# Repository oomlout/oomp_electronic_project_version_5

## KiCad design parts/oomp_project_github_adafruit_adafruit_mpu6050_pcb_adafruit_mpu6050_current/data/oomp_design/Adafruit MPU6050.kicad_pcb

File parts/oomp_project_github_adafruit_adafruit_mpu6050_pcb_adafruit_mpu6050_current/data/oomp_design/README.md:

# OOMP KiCad design copy

Open `Adafruit MPU6050.kicad_pro` (or the `.kicad_pcb` / `.kicad_sch`) in KiCad. Local OOMP libraries are under `libraries/`. Original inputs are preserved in [../original/](../original/).

Only verified unchanged installed KiCad defaults were renamed. Modified, custom, unmatched and unavailable items remain unchanged. Soldering variants are never swapped during conversion. Existing pad coordinates, nets and UUIDs are preserved.

See [conversion_report.yaml](conversion_report.yaml) for every conversion and skip. Copy this directory before editing; regeneration refuses to overwrite edited design files.

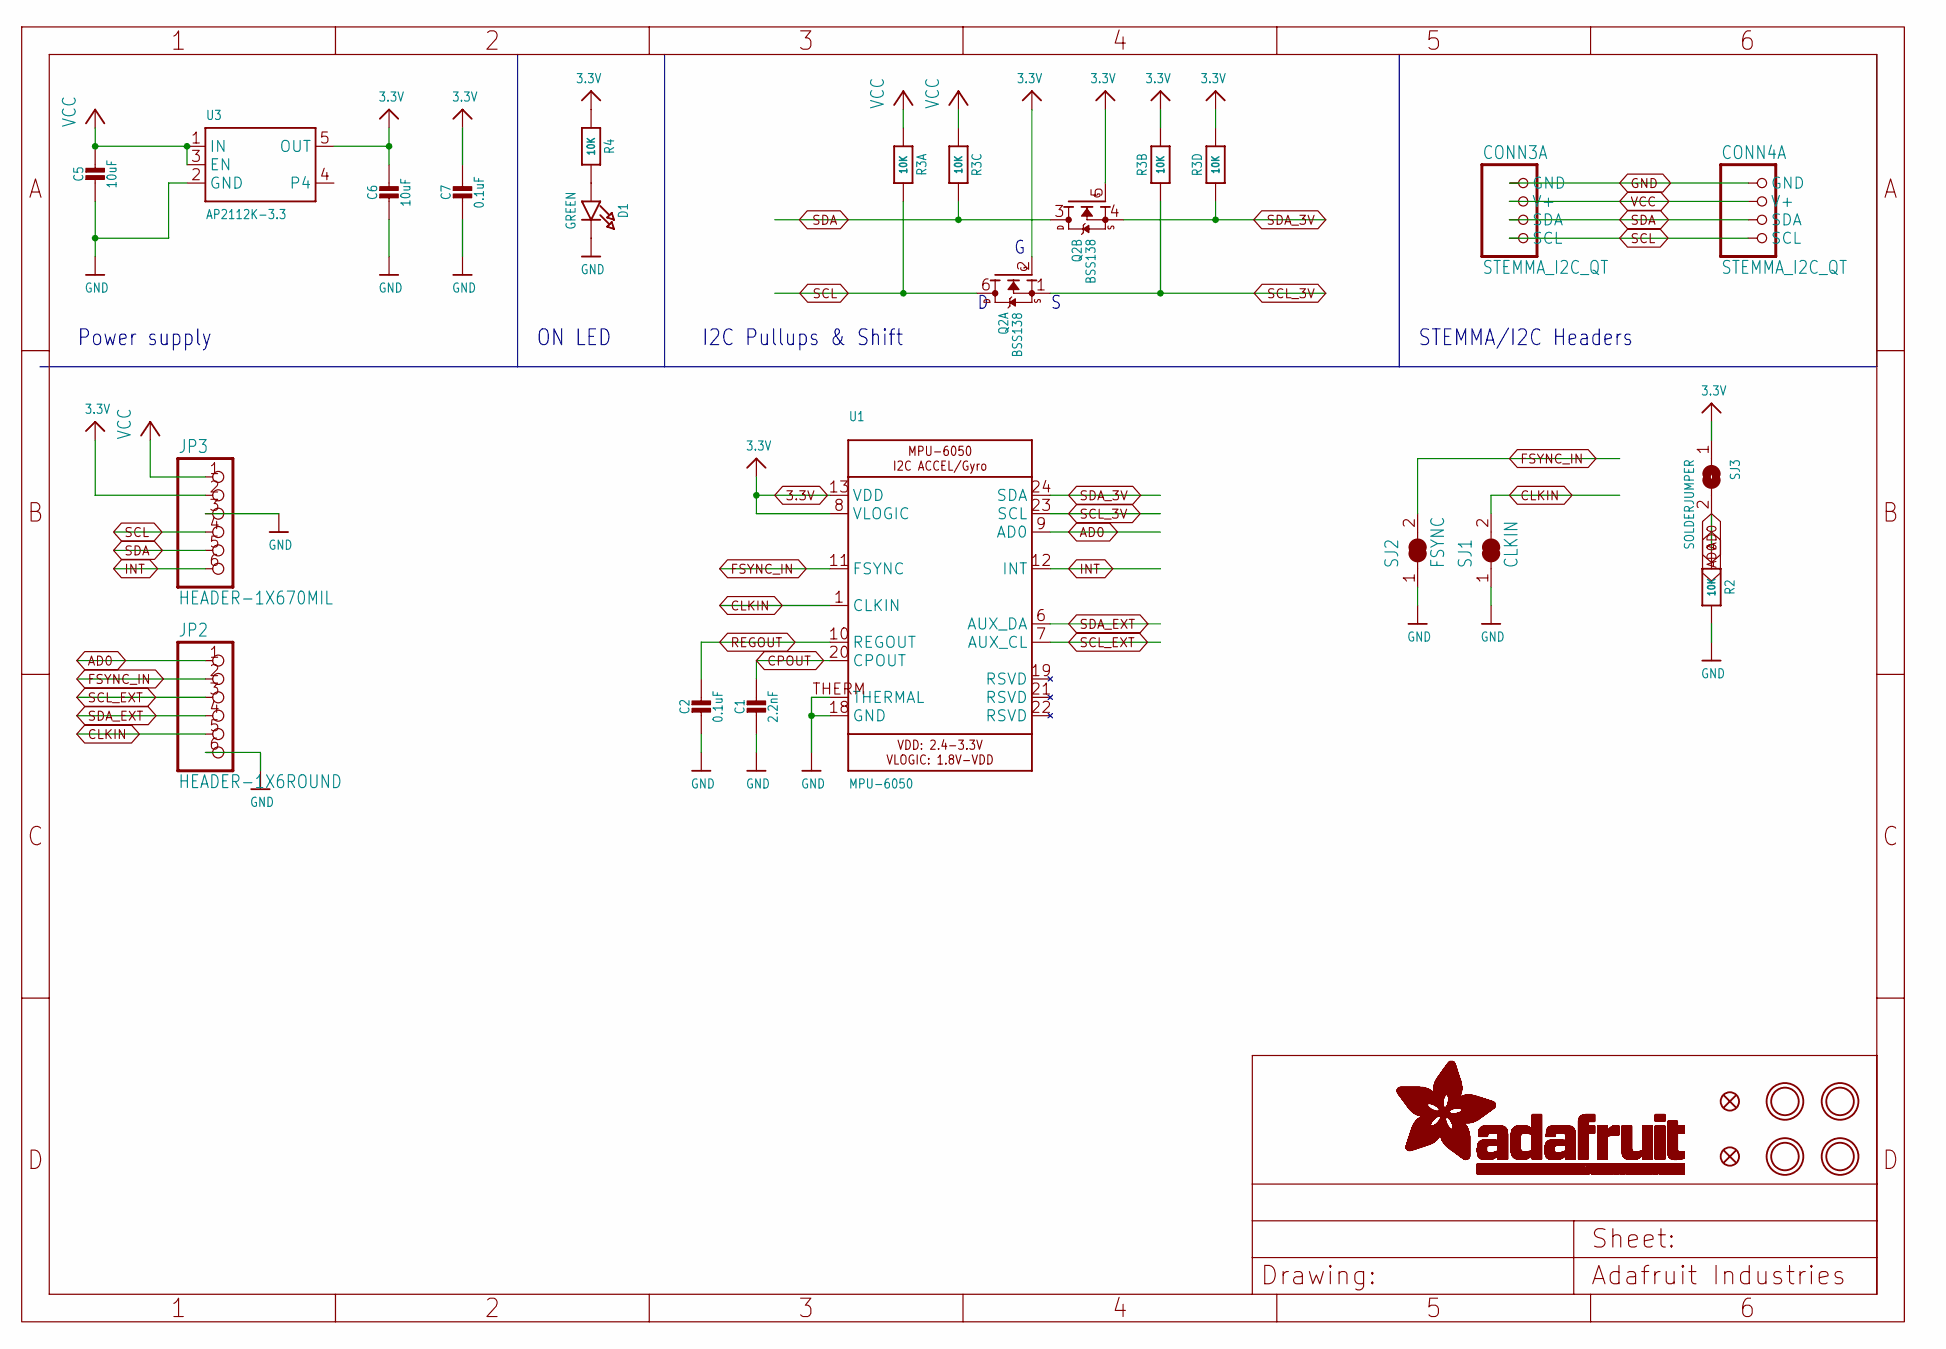
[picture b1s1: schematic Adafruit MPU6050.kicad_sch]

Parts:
C1: 2.2nF; 0603-NO
C2, C7: 0.1uF; 0603-NO
C5, C6: 10uF; 0805-NO
CONN3, CONN4: STEMMA_I2C_QT; JST_SH4
D1: GREEN; CHIPLED_0603_NOOUTLINE
FID3, FID4: FIDUCIAL_1MM
JP2: HEADER-1X6ROUND; 1X06_ROUND
JP3: HEADER-1X670MIL; 1X06_ROUND_70
Q2: BSS138; SOT363
R2, R4: 10K; 0603-NO
R3: 10K; RESPACK_4X0603
SJ1: CLKIN; SOLDERJUMPER_CLOSEDWIRE
SJ2: FSYNC; SOLDERJUMPER_CLOSEDWIRE
SJ3: SOLDERJUMPER; SOLDERJUMPER_ARROW_NOPASTE
U1: MPU-6050; QFN24_4MM_SMSC
U3: AP2112K-3.3; SOT23-5
U$39, U$40, U$42, U$43: MOUNTINGHOLE2.5; MOUNTINGHOLE_2.5_PLATED

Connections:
3.3V: C6.1, C7.1, JP3.2, Q2.2 (G), Q2.5 (G), R3.2 (1), R3.4 (1), R4.1, SJ3.1, U1.8 (VLOGIC), U1.13 (VDD), U3.5 (OUT)
AD0: JP2.1, R2.1, SJ3.2, U1.9 (AD0)
CLKIN: JP2.5, SJ1.2, U1.1 (CLKIN)
CPOUT: C1.1, U1.20 (CPOUT)
FSYNC_IN: JP2.2, SJ2.2, U1.11 (FSYNC)
GND: C1.2, C2.2, C5.2, C6.2, C7.2, CONN3.1 (GND), CONN4.1 (GND), D1.C, JP2.6, JP3.3, R2.2, SJ1.1, SJ2.1, U1.18 (GND), U1.THERM (THERMAL), U3.2 (GND)
INT: JP3.6, U1.12 (INT)
unnamed: D1.A, R4.2
REGOUT: C2.1, U1.10 (REGOUT)
SCL: CONN3.4 (SCL), CONN4.4 (SCL), JP3.4, Q2.6 (D), R3.8 (2)
SCL_3V: Q2.1 (S), R3.7 (2), U1.23 (SCL)
SCL_EXT: JP2.3, U1.7 (AUX_CL)
SDA: CONN3.3 (SDA), CONN4.3 (SDA), JP3.5, Q2.3 (D), R3.6 (2)
SDA_3V: Q2.4 (S), R3.5 (2), U1.24 (SDA)
SDA_EXT: JP2.4, U1.6 (AUX_DA)
VCC: C5.1, CONN3.2 (V+), CONN4.2 (V+), JP3.1, R3.1, R3.3 (1), U3.1 (IN), U3.3 (EN)

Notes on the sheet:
Power supply
STEMMA/I2C Headers
ON LED
I2C Pullups & Shift

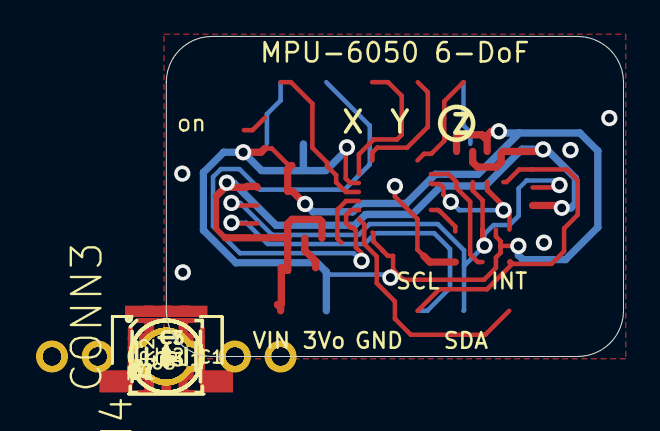
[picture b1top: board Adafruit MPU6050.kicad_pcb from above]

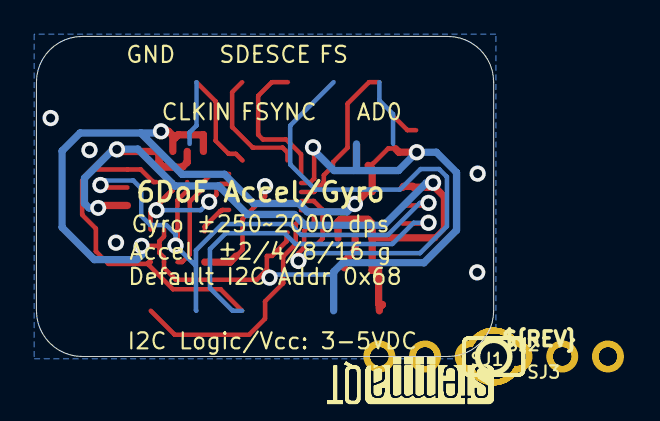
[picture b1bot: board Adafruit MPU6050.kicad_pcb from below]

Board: 2 copper layers, 25.4 x 17.8 mm, 28 parts (6 on the bottom side), 16 nets.

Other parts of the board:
U$46: PCBFEAT-REV-040
U$47, U$48: STEMMAQT

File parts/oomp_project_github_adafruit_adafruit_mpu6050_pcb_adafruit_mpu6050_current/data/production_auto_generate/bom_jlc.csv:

Comment,Designator,Footprint,LCSC Part #
,JP2,Adafruit MPU6050-import-fps:1X06_ROUND,C37208
,JP3,Adafruit MPU6050-import-fps:1X06_ROUND_70,C37208
,U$46,Adafruit MPU6050-import-fps:PCBFEAT-REV-040,
,"U$47,U$48",Adafruit MPU6050-import-fps:STEMMAQT,
0.1uF,"C2,C7",Adafruit MPU6050-import-fps:0603-NO,C14663
10K,"R2,R4",Adafruit MPU6050-import-fps:0603-NO,C98220
10K,R3,Adafruit MPU6050-import-fps:RESPACK_4X0603,C98220
10uF,"C5,C6",Adafruit MPU6050-import-fps:0805-NO,
2.2nF,C1,Adafruit MPU6050-import-fps:0603-NO,
AP2112K-3.3,U3,Adafruit MPU6050-import-fps:SOT23-5,
BSS138,Q2,Adafruit MPU6050-import-fps:SOT363,
GREEN,D1,Adafruit MPU6050-import-fps:CHIPLED_0603_NOOUTLINE,
MPU-6050,U1,Adafruit MPU6050-import-fps:QFN24_4MM_SMSC,
STEMMA_I2C_QT,"CONN3,CONN4",Adafruit MPU6050-import-fps:JST_SH4,C160404

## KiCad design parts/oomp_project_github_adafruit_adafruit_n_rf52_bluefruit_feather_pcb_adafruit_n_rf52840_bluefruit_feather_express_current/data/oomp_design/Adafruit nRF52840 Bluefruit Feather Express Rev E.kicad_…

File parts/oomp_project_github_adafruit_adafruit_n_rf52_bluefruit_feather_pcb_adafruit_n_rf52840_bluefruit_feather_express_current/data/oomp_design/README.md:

# OOMP KiCad design copy

Open `Adafruit nRF52840 Bluefruit Feather Express Rev E.kicad_pro` (or the `.kicad_pcb` / `.kicad_sch`) in KiCad. Local OOMP libraries are under `libraries/`. Original inputs are preserved in [../original/](../original/).

Only verified unchanged installed KiCad defaults were renamed. Modified, custom, unmatched and unavailable items remain unchanged. Soldering variants are never swapped during conversion. Existing pad coordinates, nets and UUIDs are preserved.

See [conversion_report.yaml](conversion_report.yaml) for every conversion and skip. Copy this directory before editing; regeneration refuses to overwrite edited design files.

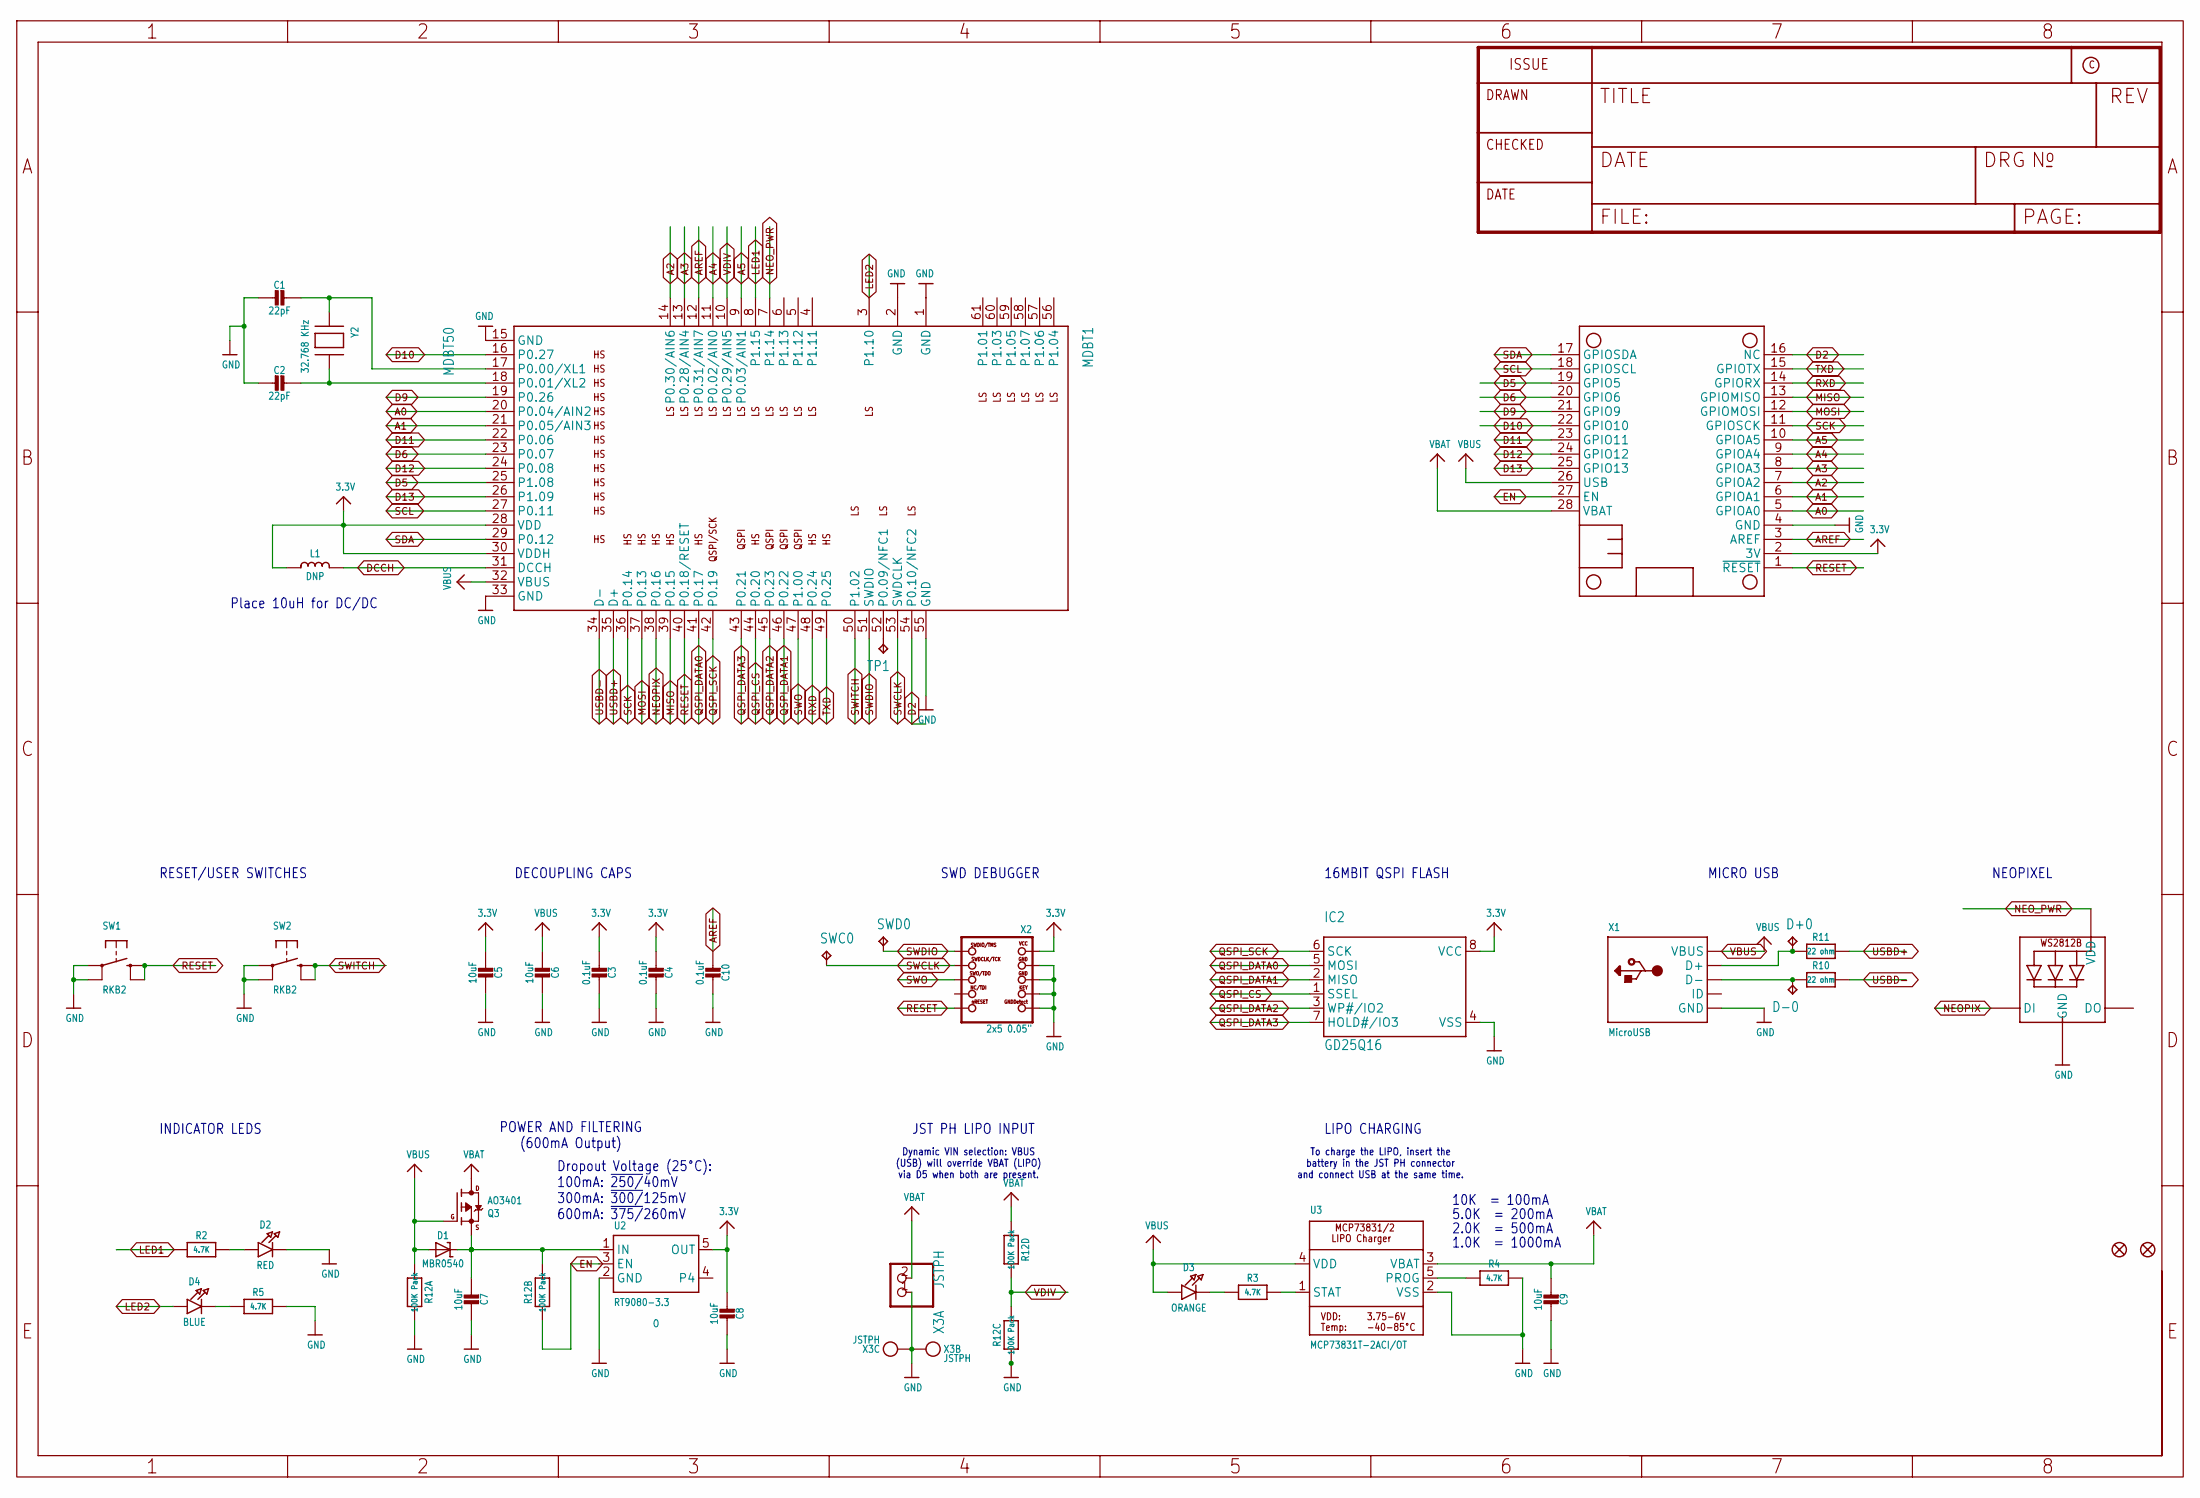
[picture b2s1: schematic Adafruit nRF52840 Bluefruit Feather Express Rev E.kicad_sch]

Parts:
C1, C2: 22pF; 0603-NO
C3, C4, C10: 0.1uF; 0603-NO
C5, C6, C7, C8, C9: 10uF; 0805-NO
D1: MBR0540; SOD-123
D2: RED; CHIPLED_0603_NOOUTLINE
D3: ORANGE; CHIPLED_0603_NOOUTLINE
D4: BLUE; CHIPLED_0603_NOOUTLINE
D+0: TPTP10R; TP10R
D-0: TPTP10R; TP10R
FID1, FID2: FIDUCIAL_1MM
IC2: GD25Q16; USON8
L1: DNP; _0805MP
LED1: WS2812B_3535FULL; LED3535_FULLPADS
MDBT1: MDBT50
MS1: FEATHERWING_NODIM
Q3: AO3401; SOT23-R
R2, R3, R4, R5: 4.7K; 0603-NO
R10, R11: 22 ohm; _0603MP
R12: 100K Pack; RESPACK_4X0603
SW1, SW2: RKB2; BTN_RKB2_4.6X2.8
SWC0: TPTP12R; TP12R
SWD0: TPTP12R; TP12R
TP1: TPTP10R; TP10R
U2: RT9080-3.3; SOT23-5; JLC_ROTATION 0
U3: MCP73831T-2ACI/OT; SOT23-5; JLC_ROTATION 0
X1: MicroUSB; 4UCONN_20329_V2
X2: 2x5 0.05"; 2X05_1.27MM_BOX_POSTS
X3: JSTPH; JSTPH2_BATT; LCSC C47647
Y2: 32.768 KHz; XTAL3215

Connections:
3.3V: C3.2, C4.2, C5.2, C8.2, IC2.8 (VCC), L1.1, MDBT1.28 (VDD), MDBT1.30 (VDDH), MS1.2 (3V), U2.5 (OUT), X2.1 (VCC)
A0: MDBT1.20 (P0.04/AIN2), MS1.5 (GPIOA0)
A1: MDBT1.21 (P0.05/AIN3), MS1.6 (GPIOA1)
A2: MDBT1.14 (P0.30/AIN6), MS1.7 (GPIOA2)
A3: MDBT1.13 (P0.28/AIN4), MS1.8 (GPIOA3)
A4: MDBT1.11 (P0.02/AIN0), MS1.9 (GPIOA4)
A5: MDBT1.9 (P0.03/AIN1), MS1.10 (GPIOA5)
AREF: C10.2, MDBT1.12 (P0.31/AIN7), MS1.3 (AREF)
D2: MDBT1.54 (P0.10/NFC2), MS1.16 (NC)
D5: MDBT1.25 (P1.08), MS1.19 (GPIO5)
D6: MDBT1.23 (P0.07), MS1.20 (GPIO6)
D9: MDBT1.19 (P0.26), MS1.21 (GPIO9)
D10: MDBT1.16 (P0.27), MS1.22 (GPIO10)
D11: MDBT1.22 (P0.06), MS1.23 (GPIO11)
D12: MDBT1.24 (P0.08), MS1.24 (GPIO12)
D13: MDBT1.26 (P1.09), MS1.25 (GPIO13)
D+: D+0.TP, R11.1, X1.D+
D-: D-0.TP, R10.1, X1.D-
DCCH: L1.2, MDBT1.31 (DCCH)
EN: MS1.27 (EN), R12.2 (1), U2.3 (EN)
GND: C1.2, C2.2, C3.1, C4.1, C5.1, C6.1, C7.1, C8.1, C9.1, C10.1, D2.C, IC2.4 (VSS), LED1.4 (GND), MDBT1.1 (GND), MDBT1.2 (GND), MDBT1.15 (GND), MDBT1.33 (GND), MDBT1.55 (GND), MS1.4 (GND), R4.2, R5.2, R12.3 (1), R12.8 (2), SW1.A, SW1.A' (P1), SW2.A, SW2.A' (P1), U2.2 (GND), U3.2 (VSS), X1.BASE@1 (GND), X1.BASE@2 (GND), X1.GND, X1.SPRT@1 (GND), X1.SPRT@2 (GND), X1.SPRT@3 (GND), X1.SPRT@4 (GND), X2.3 (GND), X2.5 (GND), X2.7 (KEY), X2.9 (GNDDETECT), X3.1, X3.NC1, X3.NC2
LED1: MDBT1.8 (P1.15), R2.1
LED2: D4.A, MDBT1.3 (P1.10)
MISO: MDBT1.39 (P0.15), MS1.13 (GPIOMISO)
MOSI: MDBT1.37 (P0.13), MS1.12 (GPIOMOSI)
unnamed: D3.C, R3.1
unnamed: D2.A, R2.2
unnamed: C1.1, MDBT1.17 (P0.00/XL1), Y2.P$1
unnamed: C2.1, MDBT1.18 (P0.01/XL2), Y2.P$2
unnamed: R3.2, U3.1 (STAT)
unnamed: R4.1, U3.5 (PROG)
unnamed: D4.C, R5.1
NEOPIX: LED1.1 (DI), MDBT1.38 (P0.16)
NEO_PWR: LED1.2 (VDD), MDBT1.7 (P1.14)
NFC2: MDBT1.52 (P0.09/NFC1), TP1.TP
QSPI_CS: IC2.1 (SSEL), MDBT1.44 (P0.20)
QSPI_DATA0: IC2.5 (MOSI), MDBT1.41 (P0.17)
QSPI_DATA1: IC2.2 (MISO), MDBT1.46 (P0.22)
QSPI_DATA2: IC2.3 (WP#/IO2), MDBT1.45 (P0.23)
QSPI_DATA3: IC2.7 (HOLD#/IO3), MDBT1.43 (P0.21)
QSPI_SCK: IC2.6 (SCK), MDBT1.42 (P0.19)
RESET: MDBT1.40 (P0.18/RESET), MS1.1 (~RESET), SW1.B (S), SW1.B' (S1), X2.10 (NRESET)
RXD: MDBT1.48 (P0.24), MS1.14 (GPIORX)
SCK: MDBT1.36 (P0.14), MS1.11 (GPIOSCK)
SCL: MDBT1.27 (P0.11), MS1.18 (GPIOSCL)
SDA: MDBT1.29 (P0.12), MS1.17 (GPIOSDA)
SWCLK: MDBT1.53 (SWDCLK), SWC0.TP, X2.4 (SWDCLK)
SWDIO: MDBT1.51 (SWDIO), SWD0.TP, X2.2 (SWDIO)
SWITCH: MDBT1.50 (P1.02), SW2.B (S), SW2.B' (S1)
SWO: MDBT1.47 (P1.00), X2.6 (SWO)
TXD: MDBT1.49 (P0.25), MS1.15 (GPIOTX)
USBD+: MDBT1.35 (D+), R11.2
USBD-: MDBT1.34 (D-), R10.2
VBAT: C9.2, MS1.28 (VBAT), Q3.3 (D), R12.4 (1), U3.3 (VBAT), X3.2
VBUS: C6.2, D1.A, D3.A, MDBT1.32 (VBUS), MS1.26 (USB), Q3.1 (G), R12.1, U3.4 (VDD), X1.VBUS
VDIV: MDBT1.10 (P0.29/AIN5), R12.5 (2), R12.6 (2)
VHI: C7.2, D1.C, Q3.2 (S), R12.7 (2), U2.1 (IN)

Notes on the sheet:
NEOPIXEL
Dynamic VIN selection: VBUS (USB) will override VBAT (LIPO) via D5 when both are present.
SWD DEBUGGER
Dropout Voltage (25°C): 100mA: ~{250/}40mV 300mA: ~{300/}125mV 600mA: ~{375/}260mV
10K = 100mA
RESET/USER SWITCHES
INDICATOR LEDS
MICRO USB
DECOUPLING CAPS
To charge the LIPO, insert the battery in the JST PH connector and connect USB at the same time.
JST PH LIPO INPUT
LIPO CHARGING
POWER AND FILTERING (600mA Output)
16MBIT QSPI FLASH
Place 10uH for DC/DC
2.0K = 500mA
1.0K = 1000mA
5.0K = 200mA

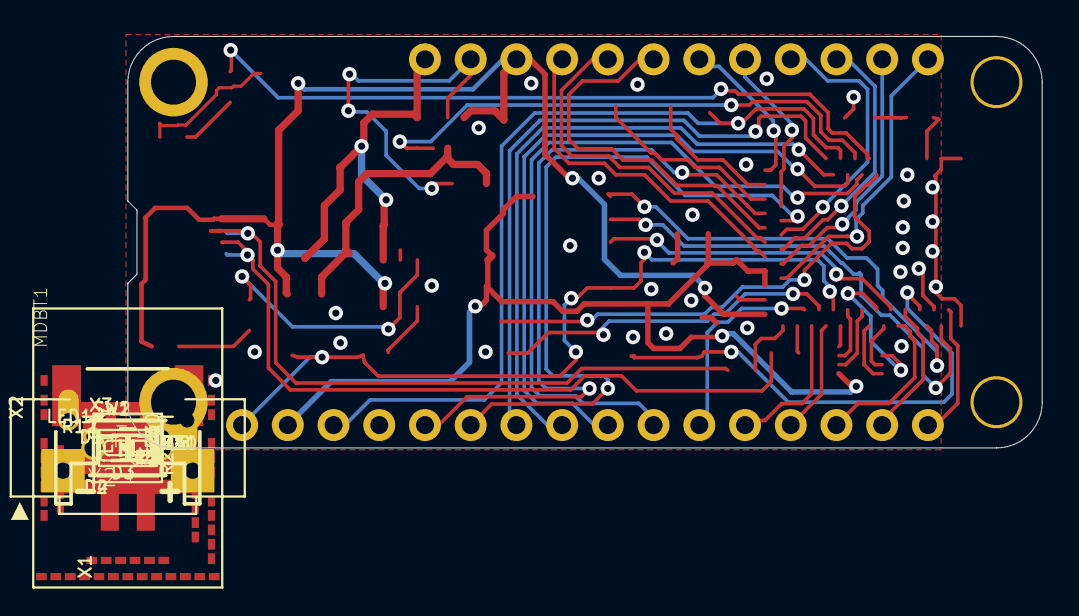
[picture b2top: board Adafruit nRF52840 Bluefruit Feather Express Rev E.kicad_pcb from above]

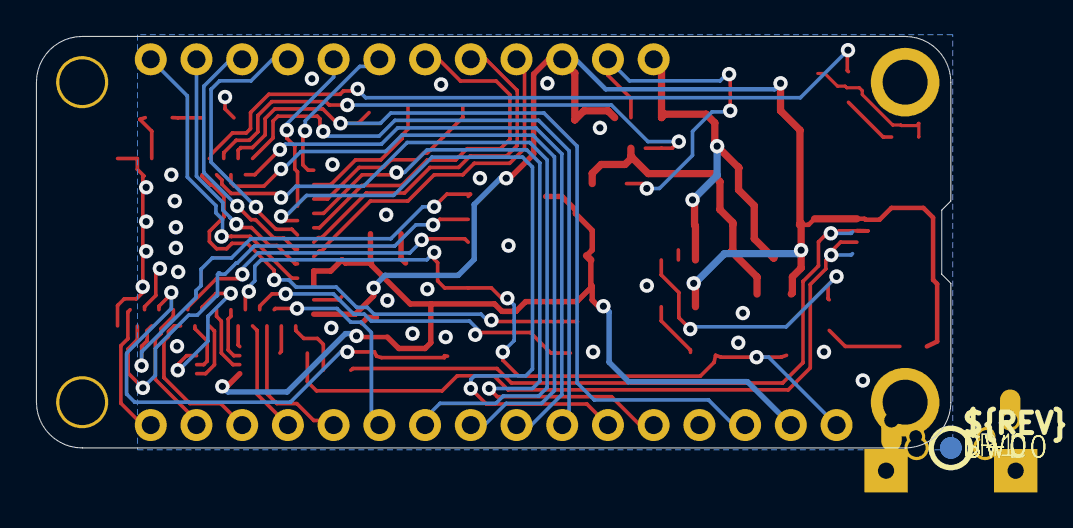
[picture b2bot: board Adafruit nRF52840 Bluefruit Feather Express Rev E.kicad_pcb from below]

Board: 2 copper layers, 50.8 x 22.9 mm, 45 parts (7 on the bottom side), 57 nets.

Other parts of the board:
U$10: PCBFEAT-REV-056
U$12: NRF52840_BOT
U$14: NRF52840_TOP

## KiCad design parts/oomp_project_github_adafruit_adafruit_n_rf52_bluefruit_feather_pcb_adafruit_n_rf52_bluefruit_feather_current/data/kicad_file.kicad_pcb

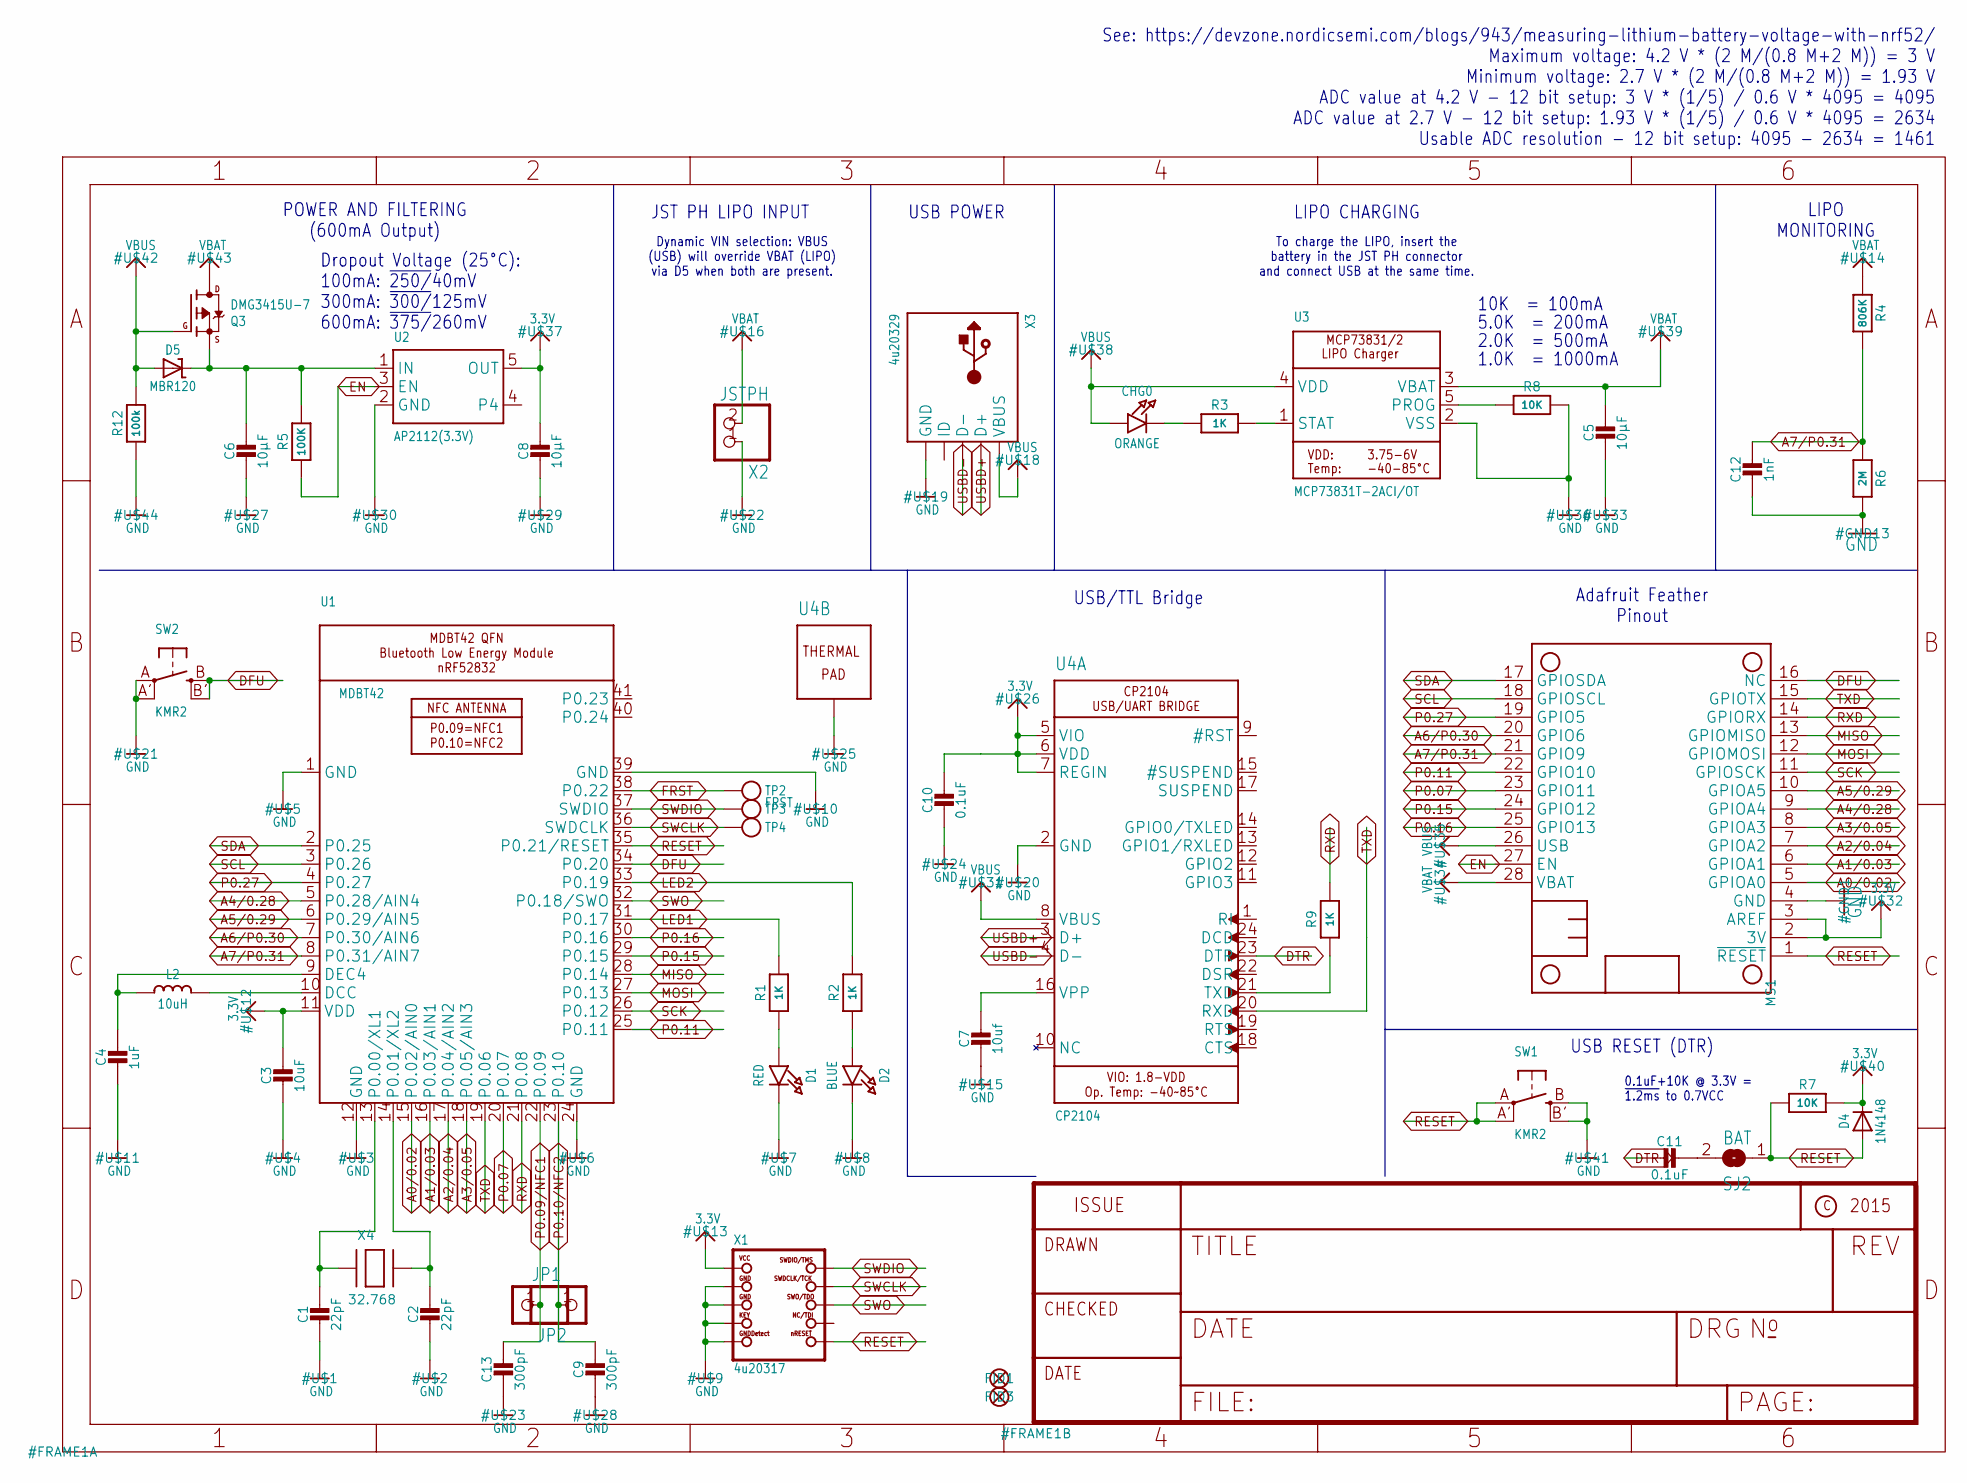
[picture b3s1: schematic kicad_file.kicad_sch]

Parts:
C1, C2: 22pF; 0603-NO
C3: 10uF; 0805-NO
C4: 1uF; 0603-NO
C5, C6, C8: 10µF; 0805-NO
C7: 10uf; 0805-NO
C9, C13: 300pF; _0603MP
C10, C11: 0.1uF; 0603-NO
C12: 1nF; 0603-NO
CHG0: ORANGE; CHIPLED_0805_NOOUTLINE
D1: RED; CHIPLED_0805_NOOUTLINE
D2: BLUE; CHIPLED_0805_NOOUTLINE
D4: 1N4148; SOD-323
D5: MBR120; SOD-123
FID1, FID3: FIDUCIAL_1MM
JP1, JP2: HEADER-1X12MM; 1X01_2MM
L2: 10uH; 0805-NO
MS1: FEATHERWING_NODIM
Q3: DMG3415U-7; SOT23-R
R1, R2, R3, R9: 1K; 0603-NO
R4: 806K; 0603-NO
R5: 100K; 0603-NO
R6: 2M; 0603-NO
R7, R8: 10K; 0603-NO
R12: 100k; 0603-NO
SJ2: BAT; SOLDERJUMPER_CLOSEDWIRE
SW1, SW2: KMR2; BTN_KMR2_4.6X2.8
TP2: FRST; PAD-1.5X2.0
TP3, TP4: TESTPOINTROUND2MM; TESTPOINT_ROUND_2MM
U1: MDBT42; BLE_MODULE_RAYTAC_MDBT42
U2: AP2112(3.3V); SOT23-5
U3: MCP73831T-2ACI/OT; SOT23-5
U4: CP2104; QFN24_4MM_SMSC
X1: 4u20317; 2X05_1.27MM_BOX_POSTS
X2: JSTPH; JSTPH2
X3: 4u20329; 4UCONN_20329_V2
X4: 32.768; XTAL3215

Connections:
3.3V: C3.1, C8.1, C10.1, D4.C, MS1.2 (3V), MS1.3 (AREF), R7.2, U1.11 (VDD), U2.5 (OUT), U4.5 (VIO), U4.6 (VDD), U4.7 (REGIN), X1.1 (VCC)
A0/0.02: MS1.5 (GPIOA0), U1.15 (P0.02/AIN0)
A1/0.03: MS1.6 (GPIOA1), U1.16 (P0.03/AIN1)
A2/0.04: MS1.7 (GPIOA2), U1.17 (P0.04/AIN2)
A3/0.05: MS1.8 (GPIOA3), U1.18 (P0.05/AIN3)
A4/0.28: MS1.9 (GPIOA4), U1.5 (P0.28/AIN4)
A5/0.29: MS1.10 (GPIOA5), U1.6 (P0.29/AIN5)
A6/P0.30: MS1.20 (GPIO6), U1.7 (P0.30/AIN6)
A7/P0.31: C12.1, MS1.21 (GPIO9), R4.2, R6.1, U1.8 (P0.31/AIN7)
DFU: MS1.16 (NC), SW2.B (S), SW2.B' (S1), U1.34 (P0.20)
DTR: C11.2, U4.23 (DTR)
EN: MS1.27 (EN), R5.1, U2.3 (EN)
FRST: TP2.P$1, U1.38 (P0.22)
GND: C1.2, C2.2, C3.2, C4.2, C5.2, C6.2, C7.2, C8.2, C9.2, C10.2, C12.2, C13.2, D1.C, D2.C, MS1.4 (GND), R6.2, R8.2, R12.1, SW1.B (S), SW1.B' (S1), SW2.A, SW2.A' (P1), U1.1 (GND), U1.12 (GND), U1.24 (GND), U1.39 (GND), U2.2 (GND), U3.2 (VSS), U4.2 (GND), U4.THERM (TP), X1.3 (GND), X1.5 (GND), X1.7 (KEY), X1.9 (GNDDETECT), X2.1, X3.BASE@1 (GND), X3.BASE@2 (GND), X3.GND, X3.SPRT@1 (GND), X3.SPRT@2 (GND), X3.SPRT@3 (GND), X3.SPRT@4 (GND)
LED1: R1.2, U1.31 (P0.17)
LED2: R2.2, U1.33 (P0.19)
MISO: MS1.13 (GPIOMISO), U1.28 (P0.14)
MOSI: MS1.12 (GPIOMOSI), U1.27 (P0.13)
unnamed: C1.1, U1.13 (P0.00/XL1), X4.P$1
unnamed: C2.1, U1.14 (P0.01/XL2), X4.P$2
unnamed: L2.2, U1.10 (DCC)
unnamed: CHG0.C, R3.1
unnamed: D1.A, R1.1
unnamed: D2.A, R2.1
unnamed: C4.1, L2.1, U1.9 (DEC4)
unnamed: R3.2, U3.1 (STAT)
unnamed: R8.1, U3.5 (PROG)
unnamed: R9.1, U4.21 (TXD)
unnamed: C11.1, SJ2.2
unnamed: C7.1, U4.16 (VPP)
P0.07: MS1.23 (GPIO11), U1.20 (P0.07)
P0.09/NFC1: C13.1, JP2.1, U1.22 (P0.09)
P0.10/NFC2: C9.1, JP1.1, U1.23 (P0.10)
P0.11: MS1.22 (GPIO10), U1.25 (P0.11)
P0.15: MS1.24 (GPIO12), U1.29 (P0.15)
P0.16: MS1.25 (GPIO13), U1.30 (P0.16)
P0.27: MS1.19 (GPIO5), U1.4 (P0.27)
RESET: D4.A, MS1.1 (~RESET), R7.1, SJ2.1, SW1.A, SW1.A' (P1), U1.35 (P0.21/RESET), X1.10 (NRESET)
RXD: MS1.14 (GPIORX), R9.2, U1.21 (P0.08)
SCK: MS1.11 (GPIOSCK), U1.26 (P0.12)
SCL: MS1.18 (GPIOSCL), U1.3 (P0.26)
SDA: MS1.17 (GPIOSDA), U1.2 (P0.25)
SWCLK: TP4.P$1, U1.36 (SWDCLK), X1.4 (SWDCLK)
SWDIO: TP3.P$1, U1.37 (SWDIO), X1.2 (SWDIO)
SWO: U1.32 (P0.18/SWO), X1.6 (SWO)
TXD: MS1.15 (GPIOTX), U1.19 (P0.06), U4.20 (RXD)
USBD+: U4.3 (D+), X3.D+
USBD-: U4.4 (D-), X3.D-
VBAT: C5.1, MS1.28 (VBAT), Q3.3 (D), R4.1, U3.3 (VBAT), X2.2
VBUS: CHG0.A, D5.A, MS1.26 (USB), Q3.1 (G), R12.2, U3.4 (VDD), U4.8 (VBUS), X3.VBUS
VIN: C6.1, D5.C, Q3.2 (S), R5.2, U2.1 (IN)

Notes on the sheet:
LIPO CHARGING
Dynamic VIN selection: VBUS (USB) will override VBAT (LIPO) via D5 when both are present.
See: https://devzone.nordicsemi.com/blogs/943/measuring-lithium-battery-voltage-with-nrf52/ Maximum voltage: 4.2 V * (2 M/(0.8 M+2 M)) = 3 V Minimum voltage: 2.7 V * (2 M/(0.8 M+2 M)) = 1.93 V ADC value at 4.2 V - 12 bit setup: 3 V * (1/5) / 0.6 V * 4095 = 4095 ADC value at 2.7 V - 12 bit setup: 1.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
Dropout Voltage (25°C): 100mA: ~{250/}40mV 300mA: ~{300/}125mV 600mA: ~{375/}260mV
USB RESET (DTR)
JST PH LIPO INPUT
USB/TTL Bridge
To charge the LIPO, insert the battery in the JST PH connector and connect USB at the same time.
USB POWER
5.0K = 200mA
10K = 100mA
0.1uF+10K @ 3.3V = ~{1.2ms} to 0.7VCC
Adafruit Feather Pinout
POWER AND FILTERING (600mA Output)
LIPO MONITORING
1.0K = 1000mA
2.0K = 500mA

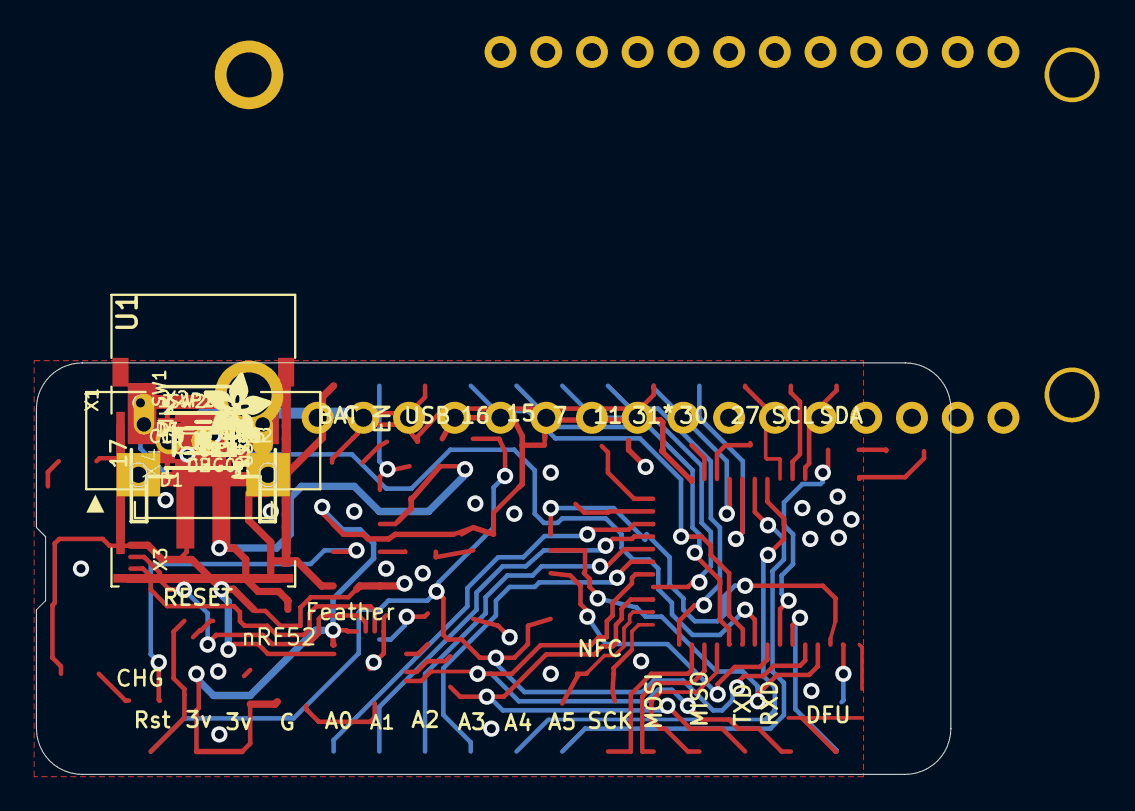
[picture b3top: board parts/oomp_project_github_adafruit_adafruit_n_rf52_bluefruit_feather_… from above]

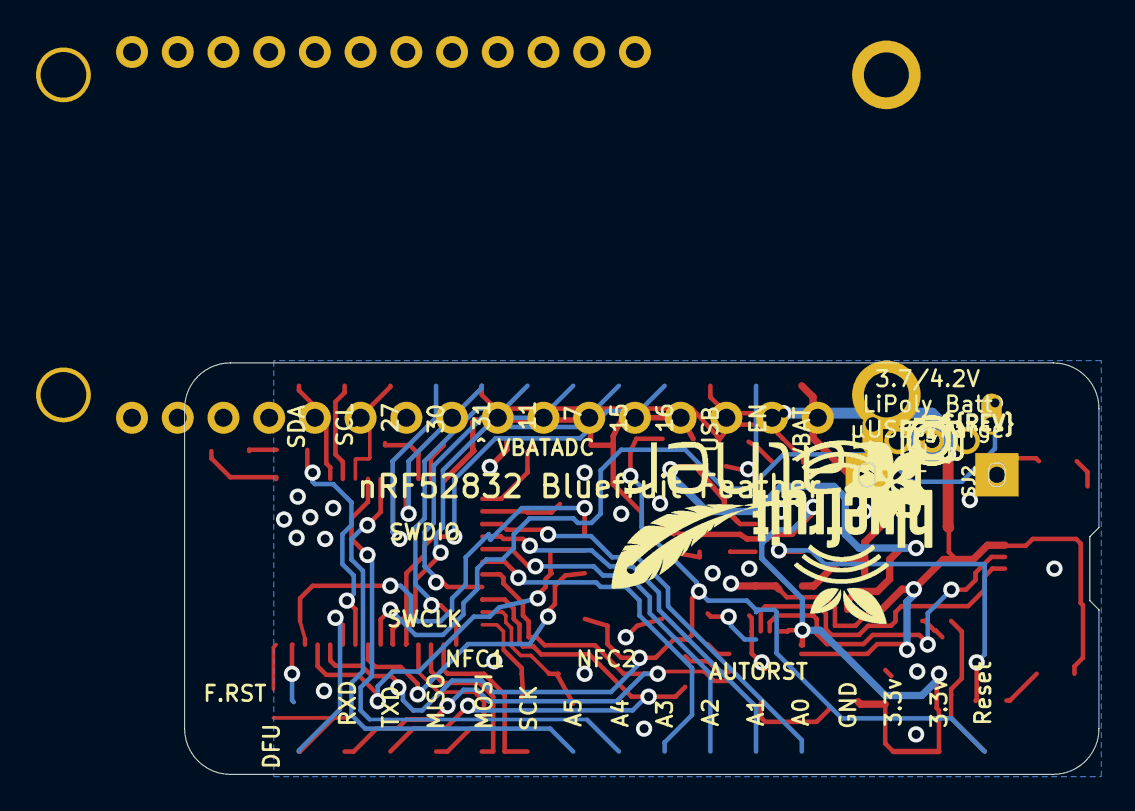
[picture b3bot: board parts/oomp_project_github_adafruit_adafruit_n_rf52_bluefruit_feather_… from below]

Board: 2 copper layers, 50.8 x 22.9 mm, 54 parts (8 on the bottom side), 51 nets.

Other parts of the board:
U$17: PCBFEAT-REV-040
U$45: BLUEFRUITLOGO_100MM
U$46: FEATHERLOGO_MED
U$47: ADAFRUIT_5MM
U$49: ADAFRUIT_3.5MM

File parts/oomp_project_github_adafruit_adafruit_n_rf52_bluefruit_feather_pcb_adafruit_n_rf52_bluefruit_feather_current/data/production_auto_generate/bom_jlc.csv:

Comment,Designator,Footprint,LCSC Part #
,"JP1,JP2",Adafruit nRF52 Bluefruit Feather-import-fps:1X01_2MM,C7501259
,U$49,Adafruit nRF52 Bluefruit Feather-import-fps:ADAFRUIT_3.5MM,
,U$47,Adafruit nRF52 Bluefruit Feather-import-fps:ADAFRUIT_5MM,
,U$45,Adafruit nRF52 Bluefruit Feather-import-fps:BLUEFRUITLOGO_100MM,
,U$46,Adafruit nRF52 Bluefruit Feather-import-fps:FEATHERLOGO_MED,
,U$17,Adafruit nRF52 Bluefruit Feather-import-fps:PCBFEAT-REV-040,
,"TP3,TP4",Adafruit nRF52 Bluefruit Feather-import-fps:TESTPOINT_ROUND_2MM,
0.1uF,"C10,C11",Adafruit nRF52 Bluefruit Feather-import-fps:0603-NO,C14663
100K,R5,Adafruit nRF52 Bluefruit Feather-import-fps:0603-NO,C25803
100k,R12,Adafruit nRF52 Bluefruit Feather-import-fps:0603-NO,C25803
10K,"R7,R8",Adafruit nRF52 Bluefruit Feather-import-fps:0603-NO,C98220
10uF,C3,Adafruit nRF52 Bluefruit Feather-import-fps:0805-NO,
10uf,C7,Adafruit nRF52 Bluefruit Feather-import-fps:0805-NO,
10uH,L2,Adafruit nRF52 Bluefruit Feather-import-fps:0805-NO,
10µF,"C5,C6,C8",Adafruit nRF52 Bluefruit Feather-import-fps:0805-NO,
1K,"R1,R2,R3,R9",Adafruit nRF52 Bluefruit Feather-import-fps:0603-NO,C2907002
1N4148,D4,Adafruit nRF52 Bluefruit Feather-import-fps:SOD-323,
1nF,C12,Adafruit nRF52 Bluefruit Feather-import-fps:0603-NO,
1uF,C4,Adafruit nRF52 Bluefruit Feather-import-fps:0603-NO,C5673
22pF,"C1,C2",Adafruit nRF52 Bluefruit Feather-import-fps:0603-NO,C105620
2M,R6,Adafruit nRF52 Bluefruit Feather-import-fps:0603-NO,
300pF,"C9,C13",Adafruit nRF52 Bluefruit Feather-import-fps:_0603MP,
32.768,X4,Adafruit nRF52 Bluefruit Feather-import-fps:XTAL3215,
4u20317,X1,Adafruit nRF52 Bluefruit Feather-import-fps:2X05_1.27MM_BOX_POSTS,
4u20329,X3,Adafruit nRF52 Bluefruit Feather-import-fps:4UCONN_20329_V2,
806K,R4,Adafruit nRF52 Bluefruit Feather-import-fps:0603-NO,
AP2112(3.3V),U2,Adafruit nRF52 Bluefruit Feather-import-fps:SOT23-5,
BLUE,D2,Adafruit nRF52 Bluefruit Feather-import-fps:CHIPLED_0805_NOOUTLINE,
CP2104,U4,Adafruit nRF52 Bluefruit Feather-import-fps:QFN24_4MM_SMSC,
DMG3415U-7,Q3,Adafruit nRF52 Bluefruit Feather-import-fps:SOT23-R,
FEATHERWING_NODIM,MS1,Adafruit nRF52 Bluefruit Feather-import-fps:FEATHERWING_NODIM,
FRST,TP2,Adafruit nRF52 Bluefruit Feather-import-fps:PAD-1.5X2.0,
JSTPH,X2,Adafruit nRF52 Bluefruit Feather-import-fps:JSTPH2,
KMR2,"SW1,SW2",Adafruit nRF52 Bluefruit Feather-import-fps:BTN_KMR2_4.6X2.8,
MBR120,D5,Adafruit nRF52 Bluefruit Feather-import-fps:SOD-123,
MCP73831T-2ACI/OT,U3,Adafruit nRF52 Bluefruit Feather-import-fps:SOT23-5,
MDBT42,U1,Adafruit nRF52 Bluefruit Feather-import-fps:BLE_MODULE_RAYTAC_MDBT42,
ORANGE,CHG0,Adafruit nRF52 Bluefruit Feather-import-fps:CHIPLED_0805_NOOUTLINE,
RED,D1,Adafruit nRF52 Bluefruit Feather-import-fps:CHIPLED_0805_NOOUTLINE,
